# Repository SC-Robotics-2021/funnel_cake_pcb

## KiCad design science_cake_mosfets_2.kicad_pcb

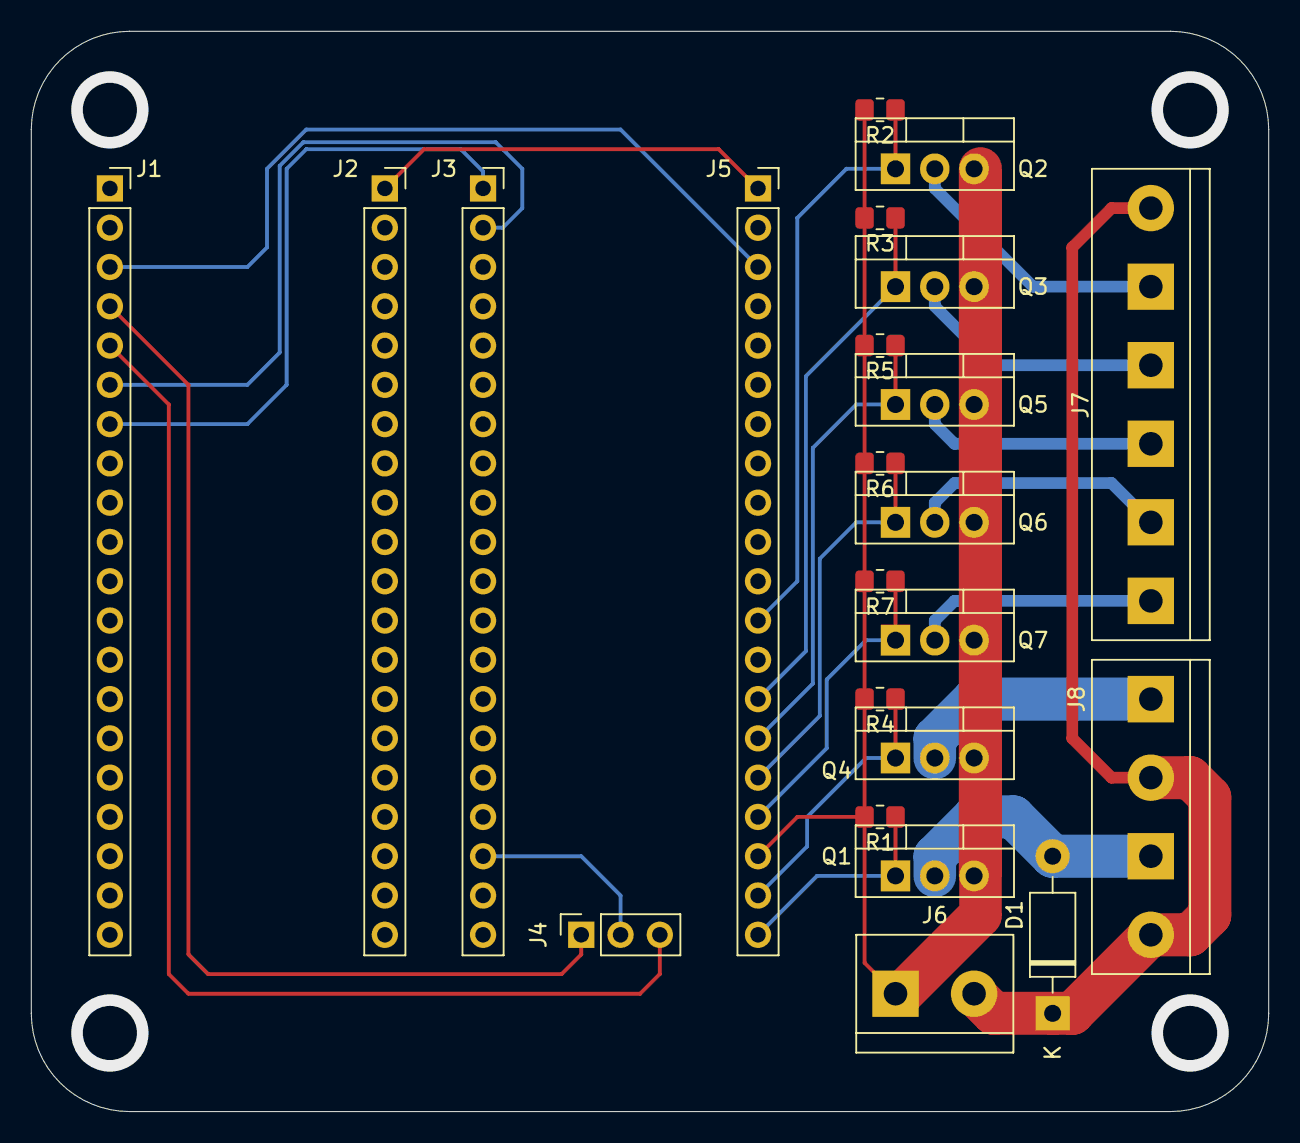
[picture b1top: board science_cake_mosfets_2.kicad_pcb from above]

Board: 2 copper layers, 80.0 x 69.9 mm, 23 parts (0 on the bottom side), 21 nets.

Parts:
D1: 1N4001; D_DO-41_SOD81_P10.16mm_Horizontal
J1, J2, J3, J5: Conn_01x20; PinSocket_1x20_P2.54mm_Vertical
J4: Conn_01x03; PinSocket_1x03_P2.54mm_Vertical
J6: Screw_Terminal_01x02; TerminalBlock_bornier-2_P5.08mm
J7: Screw_Terminal_01x06; TerminalBlock_bornier-6_P5.08mm
J8: Screw_Terminal_01x04; TerminalBlock_bornier-4_P5.08mm
Q1, Q2, Q3, Q4, Q5, Q6, Q7: IRLB8721PBF; TO-220-3_Vertical
R1, R2, R3, R4, R5, R6, R7: 10K; R_0805_2012Metric_Pad1.20x1.40mm_HandSolder

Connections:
COM: J1.3, J3.18, J4.2, J5.3, J5.18, J6.1, Q1.3, Q2.3, Q3.3, Q4.3, Q5.3, Q6.3, Q7.3, R1.2, R2.2, R3.2, R4.2, R5.2, R6.2, R7.2
D_PUMP_A: J7.5, Q2.2
D_PUMP_B: J7.4, Q3.2
D_PUMP_C: J7.3, Q5.2
D_PUMP_D: J7.2, Q6.2
D_PUMP_E: J7.1, Q7.2
D_VACUUM: J8.4, Q4.2
D_WATER: D1.2, J8.2, Q1.2
G_PUMP_A: J5.12, Q2.1, R2.1
G_PUMP_B: J5.14, Q3.1, R3.1
G_PUMP_C: J5.15, Q5.1, R5.1
G_PUMP_D: J5.16, Q6.1, R6.1
G_PUMP_E: J5.17, Q7.1, R7.1
G_VACUUM: J5.19, Q4.1, R4.1
G_WATER: J5.20, Q1.1, R1.1
PUMPS_12V: D1.1, J6.2, J7.6, J8.1, J8.3
RX: J1.7, J3.1
SWCLK: J1.4, J4.1
SWDIO: J1.5, J4.3
TX: J1.6, J3.2
VBUS: J2.1, J5.1

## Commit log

2022-05-29 added gitignore
